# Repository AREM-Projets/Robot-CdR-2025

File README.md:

# Robot-CdR-2025

Repo contenant l'ensemble des documents liés au robot de la coupe de France de Robotique 2025

## Liens utiles

* [Notion des tâches à réaliser](https://gevorgs.notion.site/2f7c12f6feff4595ba645344655ddd17?v=308f1cf20fb54248941d14f6b965dd2d)
* [Lien vers le règlement](https://www.coupederobotique.fr/accueil/le-concours/reglement-2025/)

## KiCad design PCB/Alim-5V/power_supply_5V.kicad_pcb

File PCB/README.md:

# PCB utilisés pour le robot de la CdR 2025

* PCB Alimentation
* PCB Shield STM32 Embase

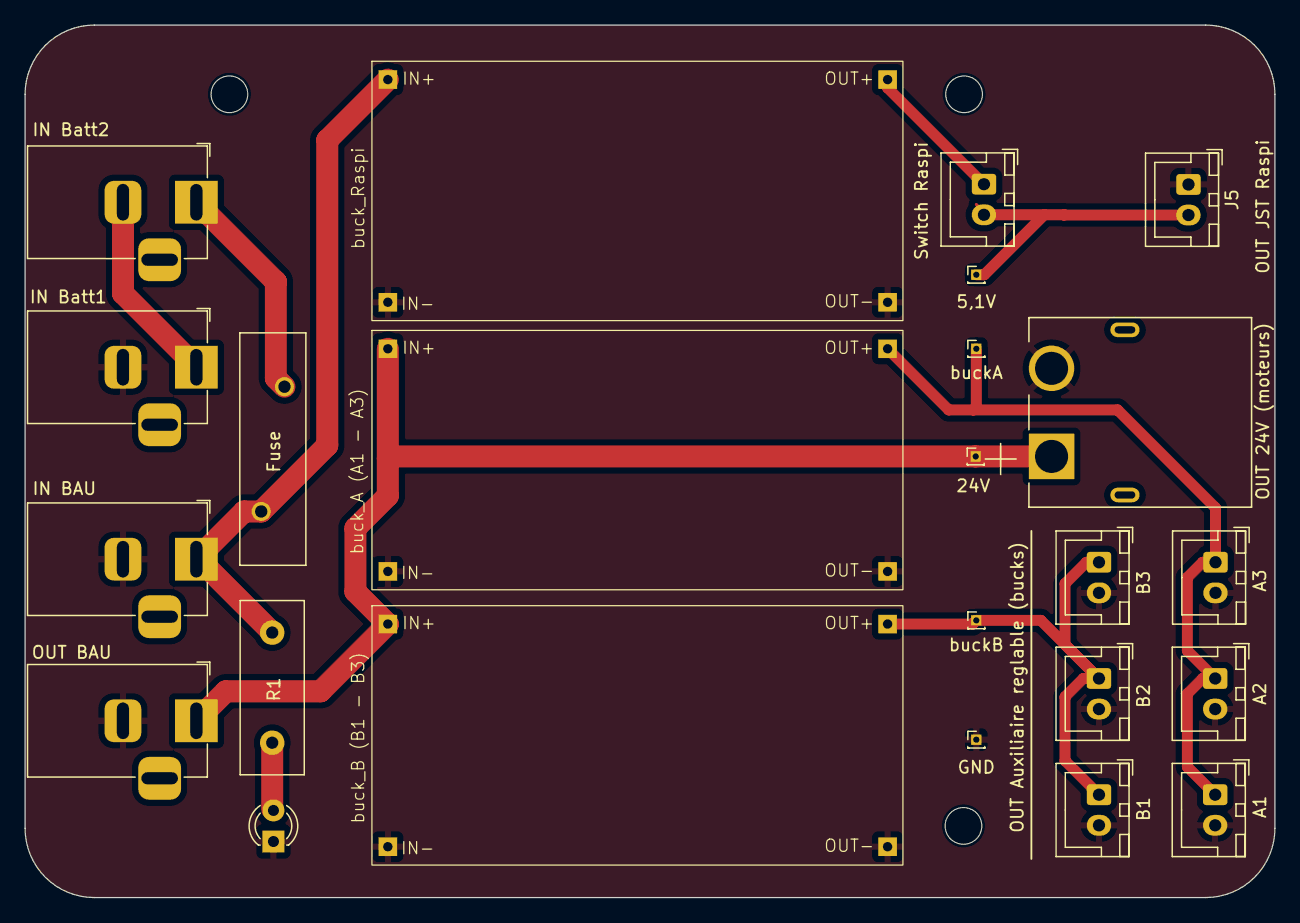
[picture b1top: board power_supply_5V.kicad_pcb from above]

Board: 2 copper layers, 102.2 x 71.3 mm, 27 parts (0 on the bottom side), 10 nets.

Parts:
5,1V, 24V: Conn_01x01; PinHeader_1x01_P1.00mm_Vertical
D1: LED; LED_D3.0mm
F1: Fuse; Fuse_BelFuse_0ZRE0100FF_L18.7mm_W5.1mm
GND: Conn_01x01; PinHeader_1x01_P1.00mm_Vertical
H1, H2, H3: MountingHole; MountingHole_3mm
J1, J11: Conn_Jack; BarrelJack_Horizontal
J3, J4, J5, J12, J14, J16, J17, J18: Conn_JST_XH_2_pins; JST_XH_B2B-XH-A_1x02_P2.50mm_Vertical
J6: Conn_01x02_Pin; AMASS_XT60PW-M
J8, J13: Conn_01x02_Pin; BarrelJack_Horizontal
R1: R; R_Box_L14.0mm_W5.0mm_P9.00mm
U1, U2, U3: HW_411
buckA: Conn_01x01; PinHeader_1x01_P1.00mm_Vertical
buckB: Conn_01x01; PinHeader_1x01_P1.00mm_Vertical

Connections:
GND: D1.1 (K), GND.1, J3.2, J5.1, J6.2, J8.2, J11.2, J12.2, J13.2, J14.2, J16.2, J17.2, J18.2, U1.2 (IN-), U1.4 (OUT-), U2.2 (IN-), U2.4 (OUT-), U3.2 (IN-), U3.4 (OUT-)
unnamed: D1.2 (A), R1.2
unnamed: F1.1, J1.1
unnamed: J1.2, J11.1
unnamed: J4.1, U1.3 (OUT+)
unnamed: F1.2, J8.1, R1.1, U1.1 (IN+)
unnamed: J3.1, J12.1, J14.1, U2.3 (OUT+), buckB.1
unnamed: 24V.1, J6.1, J13.1, U2.1 (IN+), U3.1 (IN+)
unnamed: J16.1, J17.1, J18.1, U3.3 (OUT+), buckA.1
unnamed: 5,1V.1, J4.2, J5.2

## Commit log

2024-10-21 Ajout : PCB, Modèles 3D, Documentation initiale
2024-11-17 Ajout: push initial pour le LIDAR
    Elouan MARRON (je push depuis la RasPi, il faut se mettre d'accord sur une adresse mail pour l'instant je laisse la mienne)
2024-11-17 Ajout: submodule pour le SDK
2024-11-20 feat: timestamp
    Ajout des timestamps dans la récupération des données, à voir si on veut un timestamp par données ou juste le premier suffit
2024-11-24 Ajout code embase ancien
2024-11-24 Changement nom fichier. Code initial embase par acoups
2024-11-24 Correction de nommage et de références dans le projet CubeIDE
2024-11-25 Ajout fichiers 3D base balises plateau
2024-11-25 nouvelle version code embase ultra simple sans file de taches (directement piloté par le port usb)
2024-12-08 Ajout lien vers Notion dans README
2024-12-08 Ajout lien reglement
2024-12-15 update code embase light
2024-12-15 ajout commande recup position
2024-12-16 debut nettoyage code embase
2024-12-16 nettoyage code et ajout calcul position
2024-12-16 update pour le calcul de position. Il reste a revoir le calcul du heading & Cie
2024-12-17 Update systeme positionnement ok
2025-01-30 test controle vitesse
2025-03-03 tentative correction translation laterale
2025-03-03 Branche de recup pour revenir a une version fonctionnelle
2025-03-03 clean
2025-03-03 fichiers a jour
2025-03-07 ajout code python de base pour controle de l'embase
2025-03-07 mouvement de demo
2025-03-08 trajectoire rectangulaire
2025-03-09 Update controle vitesse sans magouille
2025-03-11 update odometrie
2025-03-11 rotation 360 test ok
2025-03-14 feat: described LIDAR procedure
    Dans l'idée, il faudrait suivre cette procédure, c'est la plus simple. Mais tout est ouvert à suggestions.
2025-03-18 ajout support banderole, impression en cours
2025-03-20 Debut debug embase
2025-03-20 Debug odométrie ok
2025-03-20 Odométrie OK !
2025-03-20 debut classe Embase
2025-03-22 Debut classe Autopilot et testbench
2025-03-23 nettoyage
2025-03-23 Ajout driver lidar et chaine de compilation + script python de test du driver
2025-03-28 Ajout nouveau diagramme fonctionnement
2025-04-03 remise a niveau repo
2025-04-22 ajout du generateur
2025-05-28 added get_status function, call at beginning of code
